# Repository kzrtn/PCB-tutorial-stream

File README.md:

# PCB-tutorial-stream
From a live stream where I taught basic PCB design. Live stream VOD here: https://youtu.be/Ov2vdJQmaAw

Features:
- Atmega32u2
- 2 Hotswap sockets
- USB-C

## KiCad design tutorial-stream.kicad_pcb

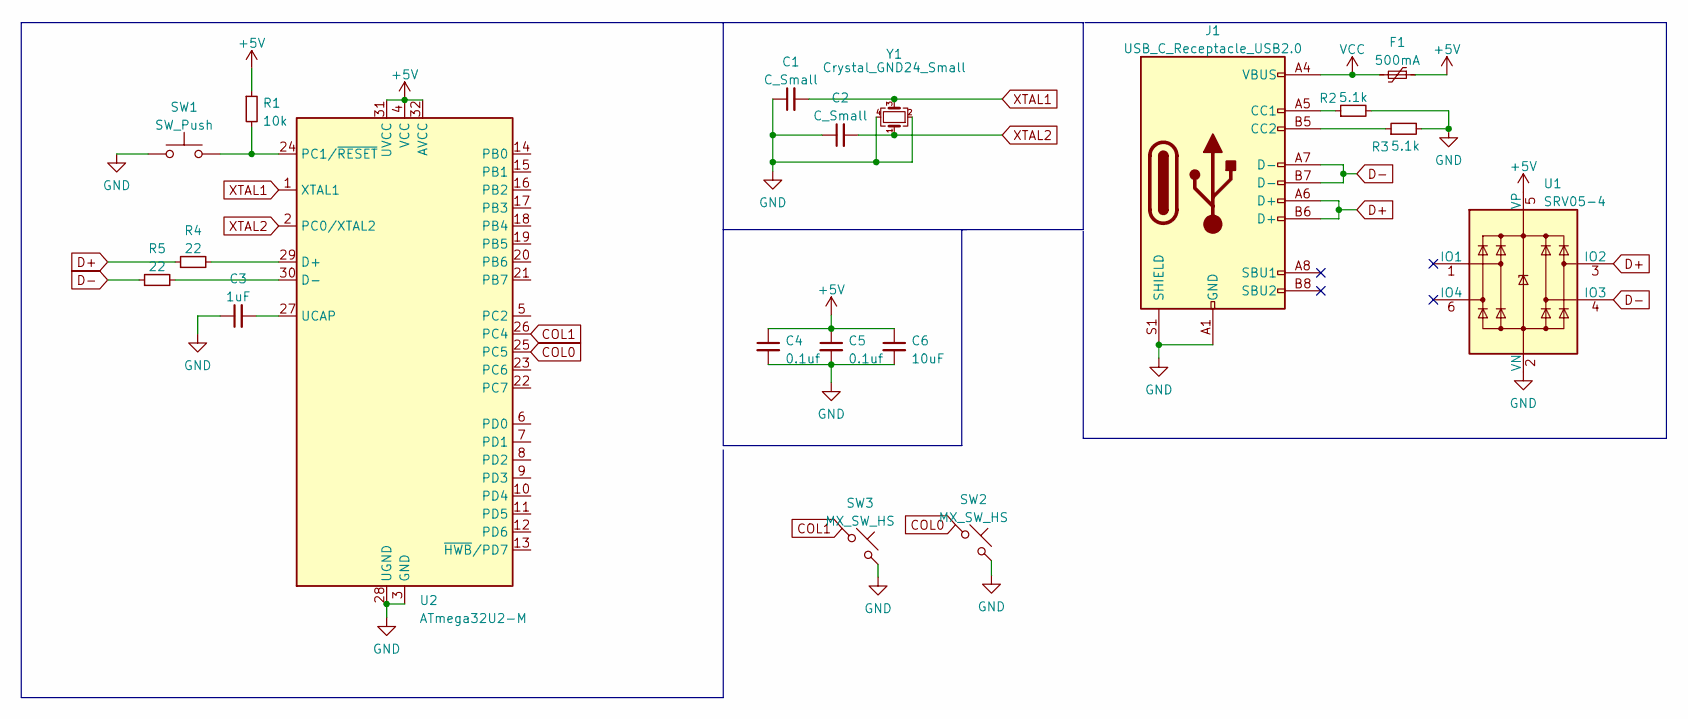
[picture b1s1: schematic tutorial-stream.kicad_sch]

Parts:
C1, C2: C_Small; C_0402_1005Metric_Pad0.74x0.62mm_HandSolder
C3: 1uF; C_0402_1005Metric_Pad0.74x0.62mm_HandSolder
C4, C5: 0.1uf; C_0402_1005Metric_Pad0.74x0.62mm_HandSolder
C6: 10uF; C_0402_1005Metric_Pad0.74x0.62mm_HandSolder
F1: 500mA; Fuse_0402_1005Metric
J1: USB_C_Receptacle_USB2.0; USB_C_Receptacle_HRO_TYPE-C-31-M-12
R1: 10k; R_0402_1005Metric_Pad0.72x0.64mm_HandSolder
R2, R3: 5.1k; R_0402_1005Metric_Pad0.72x0.64mm_HandSolder
R4, R5: 22; R_0402_1005Metric_Pad0.72x0.64mm_HandSolder
SW1: SW_Push; SW_SPST_SKQG_WithStem
SW2, SW3: MX_SW_HS; SW_MX_HS_1u
U1: SRV05-4; SOT-23-6-routable
U2: ATmega32U2-M; QFN-32-1EP_5x5mm_P0.5mm_EP3.1x3.1mm
Y1: Crystal_GND24_Small; Crystal_SMD_3225-4Pin_3.2x2.5mm_HandSoldering

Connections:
+5V: C4.1, C5.1, C6.1, F1.1, R1.1, U1.5 (VP), U2.4 (VCC), U2.31 (UVCC), U2.32 (AVCC)
COL0: SW2.1, U2.25 (PC5)
COL1: SW3.1, U2.26 (PC4)
D+: J1.A6 (D+), J1.B6 (D+), R4.1, U1.3 (IO2)
D-: J1.A7 (D-), J1.B7 (D-), R5.1, U1.4 (IO3)
GND: C1.1, C2.1, C3.1, C4.2, C5.2, C6.2, J1.A1 (GND), J1.A12 (GND), J1.B1 (GND), J1.B12 (GND), J1.S1 (SHIELD), R2.2, R3.2, SW1.1, SW2.2, SW3.2, U1.2 (VN), U2.3 (GND), U2.28 (UGND), U2.33 (GND), Y1.2, Y1.4
unnamed: C3.2, U2.27 (UCAP)
unnamed: J1.A5 (CC1), R2.1
unnamed: J1.B5 (CC2), R3.1
unnamed: R1.2, SW1.2, U2.24 (PC1/~RESET)
unnamed: R4.2, U2.29 (D+)
unnamed: R5.2, U2.30 (D-)
VCC: F1.2, J1.A4 (VBUS), J1.A9 (VBUS), J1.B4 (VBUS), J1.B9 (VBUS)
XTAL1: C1.2, U2.1 (XTAL1), Y1.3
XTAL2: C2.2, U2.2 (PC0/XTAL2), Y1.1

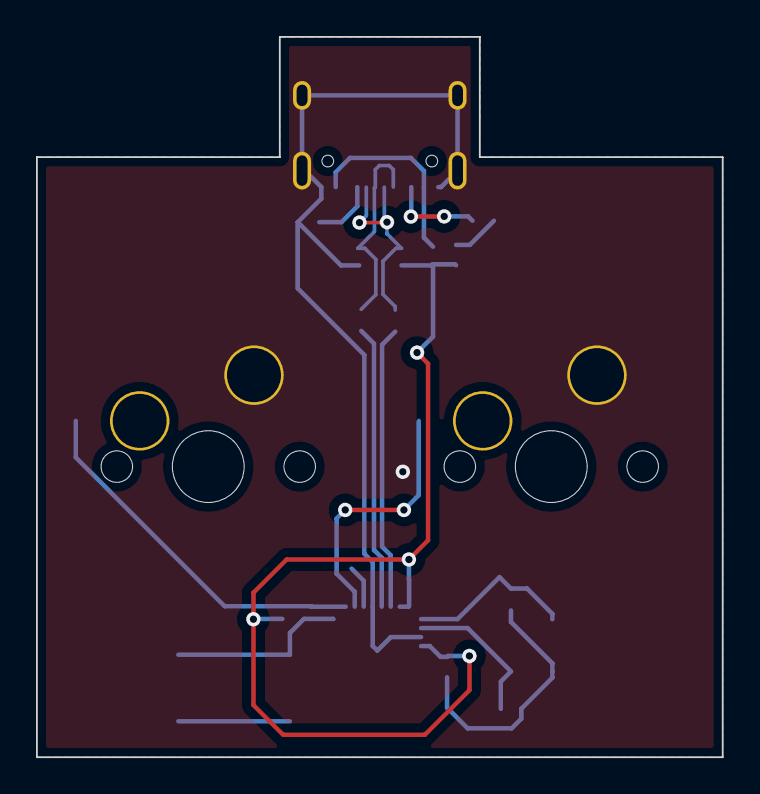
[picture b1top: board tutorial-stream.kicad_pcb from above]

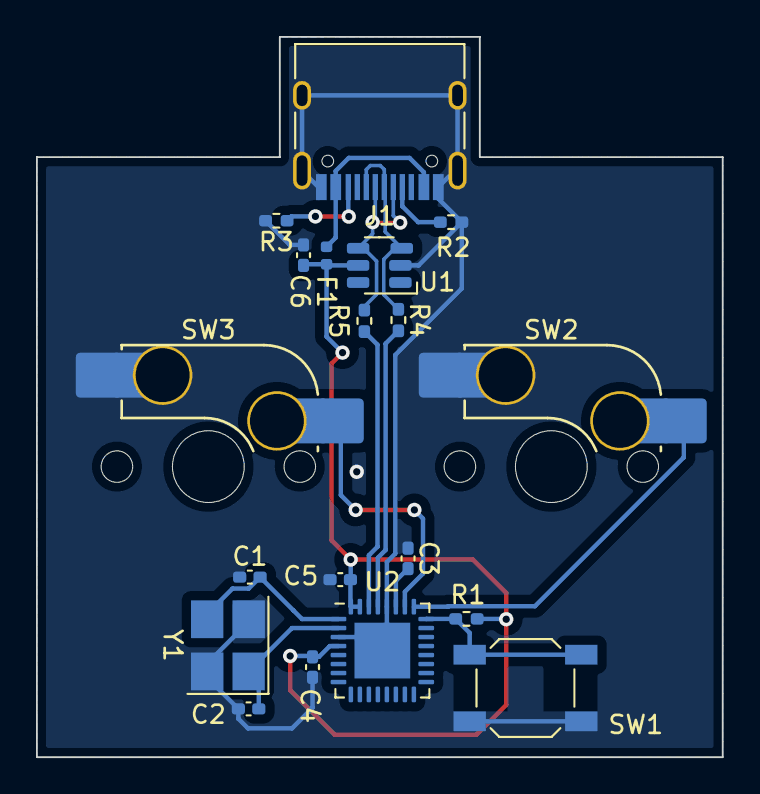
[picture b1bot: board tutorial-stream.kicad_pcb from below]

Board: 2 copper layers, 38.1 x 40.0 mm, 19 parts (19 on the bottom side), 15 nets.

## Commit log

2022-07-01 Added all the files
2022-07-01 Ignore local backup files
